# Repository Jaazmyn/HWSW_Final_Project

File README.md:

# HWSW_Final_Project
## Breathe with Heart
## **Introduction**

This device is designed to help people reduce anxiety during a panic attack by guiding them to breathe mindfully. It tracks the user’s heartbeat in real-time and provides feedback (such as dimming lights) to prompt users to practice breathing meditation.
- LED light: Display users' anxiety level and suggest breathing tempo.
- Stepper Gauge Needle: Display users' anxiety level.

## **Sensor**

**PPG(photoplethysmography)-MAX30102** is chosed for this project. The sensor senses changes in blood flow caused by heartbeats using light absorption. It calculates:
- **Heart Rate (BPM)**
- **Heart Rate Variability (HRV)** for stress analysis.
- Optionally, **oxygen saturation (SpO2)** and **perfusion index (PI)**

When user hold the device with their hands, the sensor will be sensing their thumbs to progress the data to ESP32 and analyse users' status.

## **Display**

- **RGB LED Strip**
This color of the RGB LED display the user's anxiety level from green to red. The brightness of the light changes along with the suggested breathing tempo.
- **Stepper Gauge Needle**
This needle display users' anxiety percentage according to the calculated **HRV**.

## **Diagram**

- How it will work

- Systems Architecture Diagram

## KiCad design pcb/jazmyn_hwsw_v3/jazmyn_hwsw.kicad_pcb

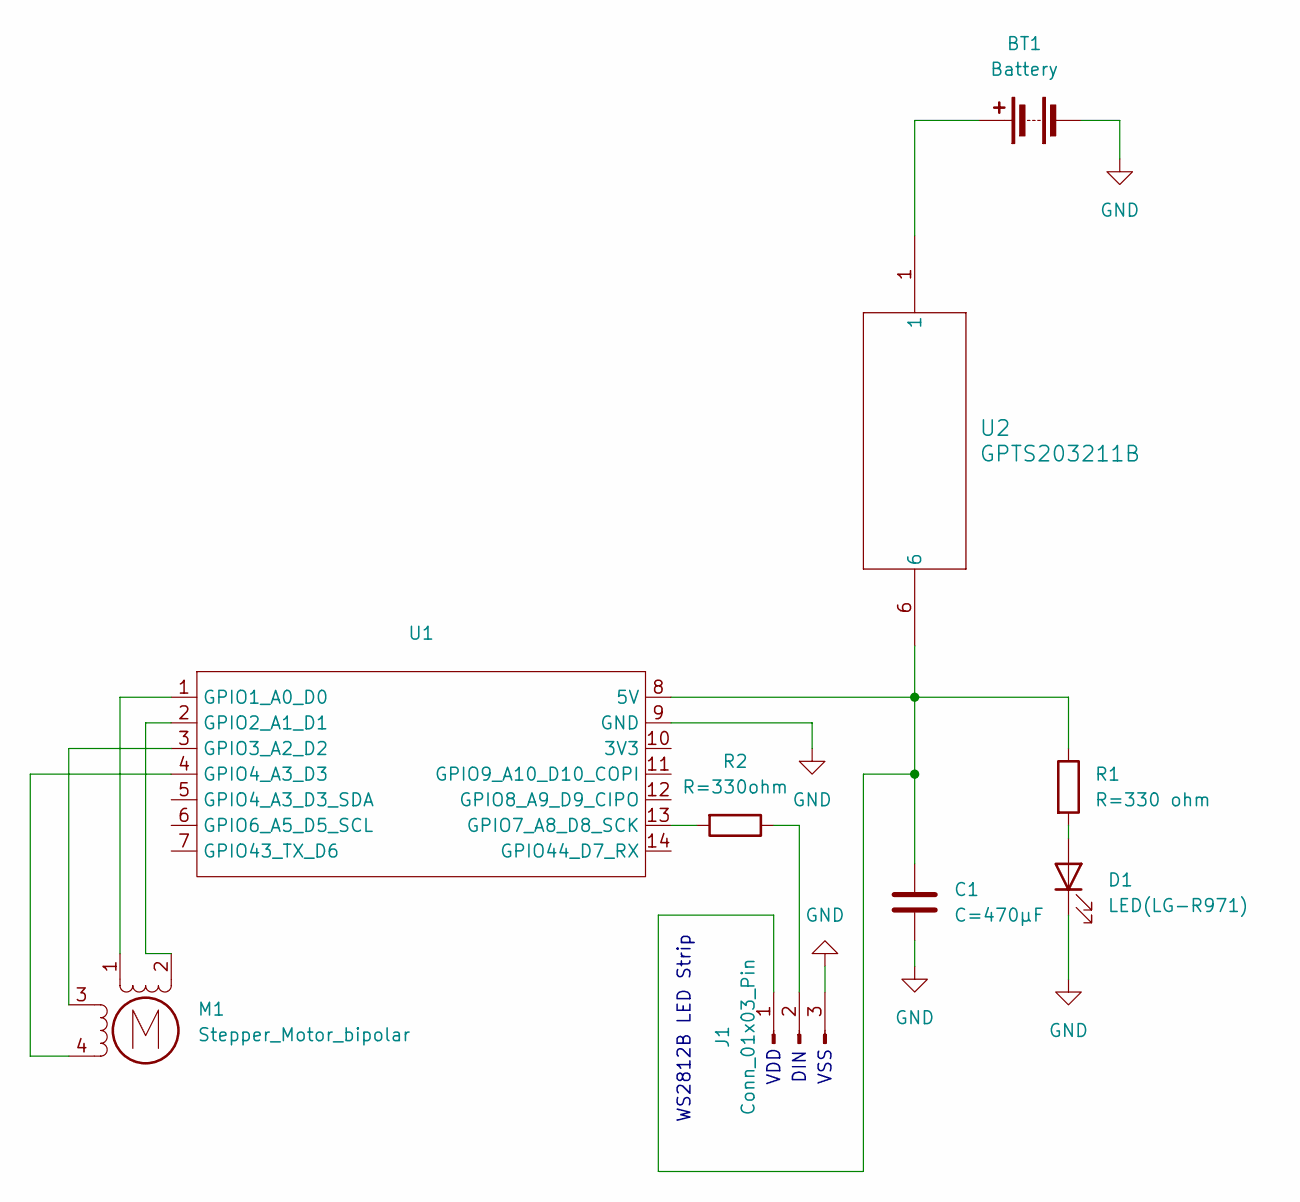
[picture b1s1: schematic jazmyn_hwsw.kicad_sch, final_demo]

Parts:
BT1: Battery; JST_PH_B2B-PH-K_1x02_P2.00mm_Vertical
C1: C=470µF; C_0805_2012Metric_Pad1.18x1.45mm_HandSolder
D1: LED(LG-R971); LED_0805_2012Metric_Pad1.15x1.40mm_HandSolder
J1: Conn_01x03_Pin; PinHeader_1x03_P2.54mm_Vertical_SMD_Pin1Right
M1: Stepper_Motor_bipolar; x27_stepper
R1: R=330 ohm; R_0805_2012Metric_Pad1.20x1.40mm_HandSolder
R2: R=330ohm; R_0805_2012Metric_Pad1.20x1.40mm_HandSolder
U1: XIAO_ESP32_SENSE
U2: GPTS203211B; SWITCH_03211B

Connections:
GND: BT1.2 (-), C1.2, D1.1 (K), J1.3, U1.9 (GND)
unnamed: BT1.1 (+), U2.1
unnamed: D1.2 (A), R1.2
unnamed: C1.1, J1.1, R1.1, U1.8 (5V), U2.6
unnamed: J1.2, R2.1
unnamed: M1.2 (-), U1.2 (GPIO2_A1_D1)
unnamed: M1.1, U1.1 (GPIO1_A0_D0)
unnamed: M1.3, U1.3 (GPIO3_A2_D2)
unnamed: M1.4, U1.4 (GPIO4_A3_D3)
unnamed: R2.2, U1.13 (GPIO7_A8_D8_SCK)

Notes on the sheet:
VDD
WS2812B LED Strip
DIN
VSS

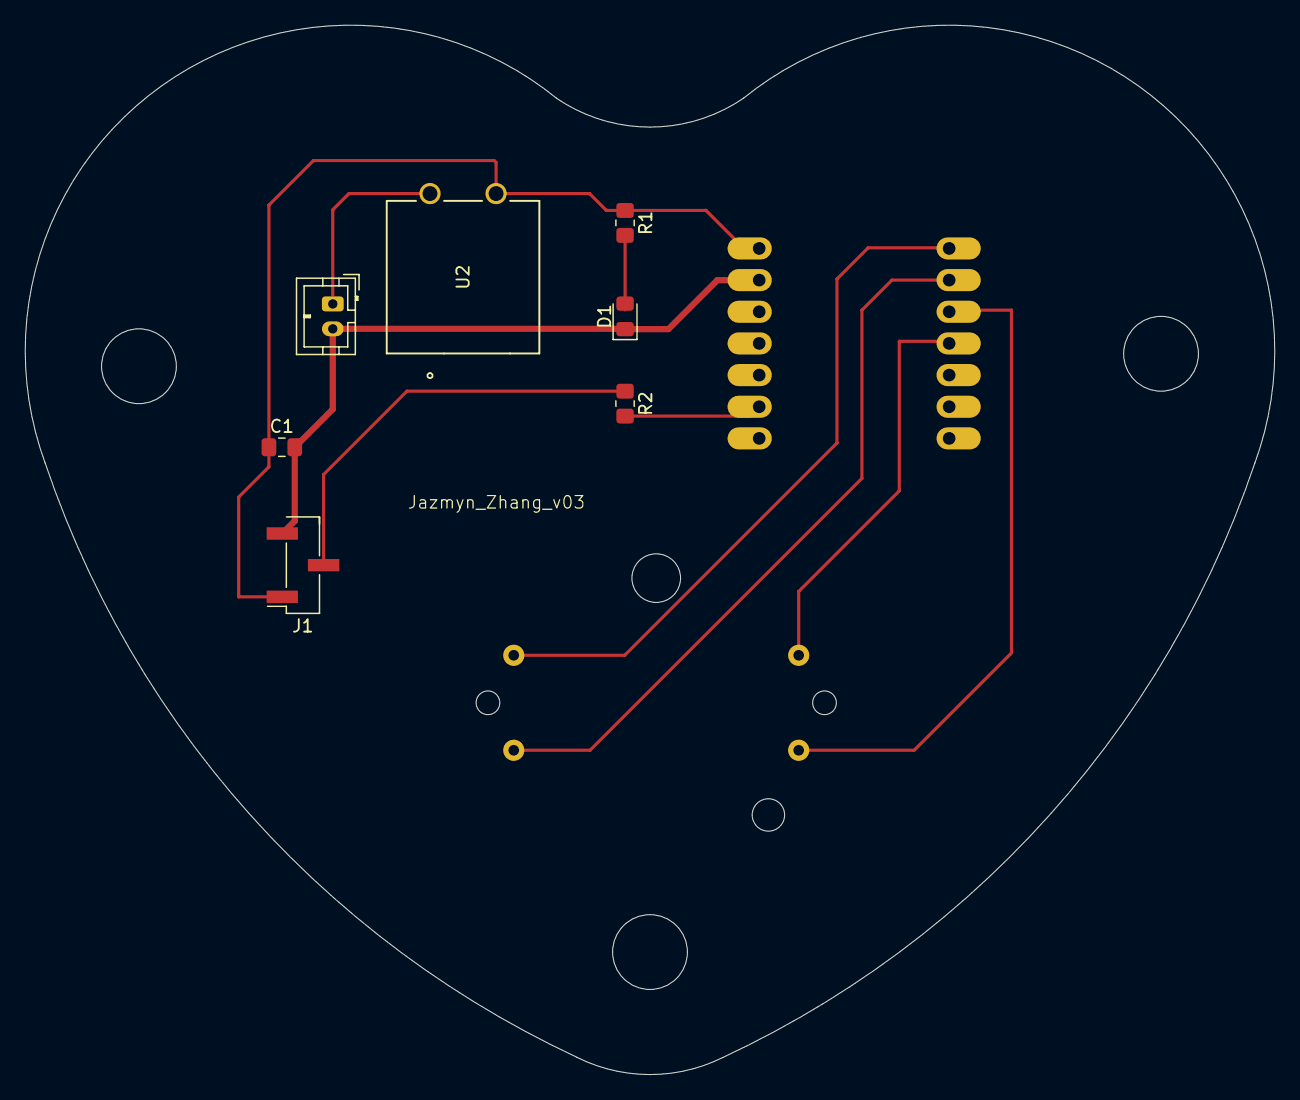
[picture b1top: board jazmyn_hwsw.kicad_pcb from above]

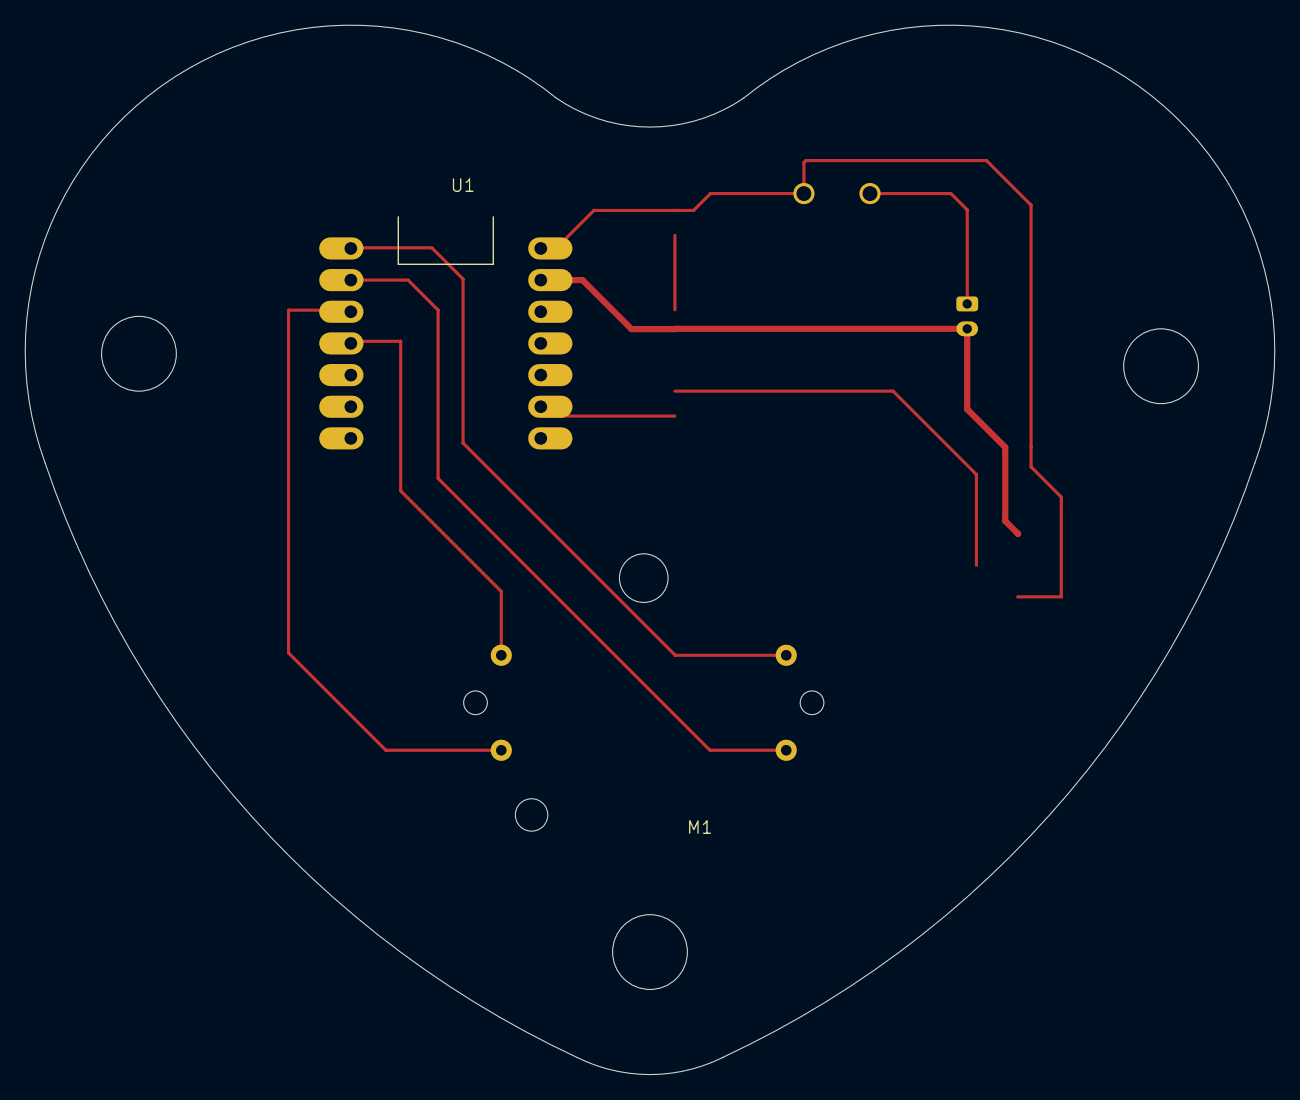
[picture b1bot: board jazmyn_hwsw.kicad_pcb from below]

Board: 2 copper layers, 100.2 x 84.2 mm, 9 parts (2 on the bottom side), 10 nets.

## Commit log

2025-01-21 test
2025-01-22 Add system architecture and datasheet
2025-01-22 Edit README
2025-01-28 Add pcb folder and update datasheet
2025-01-29 Schematic updated
2025-03-11 Update code datasheet and src
